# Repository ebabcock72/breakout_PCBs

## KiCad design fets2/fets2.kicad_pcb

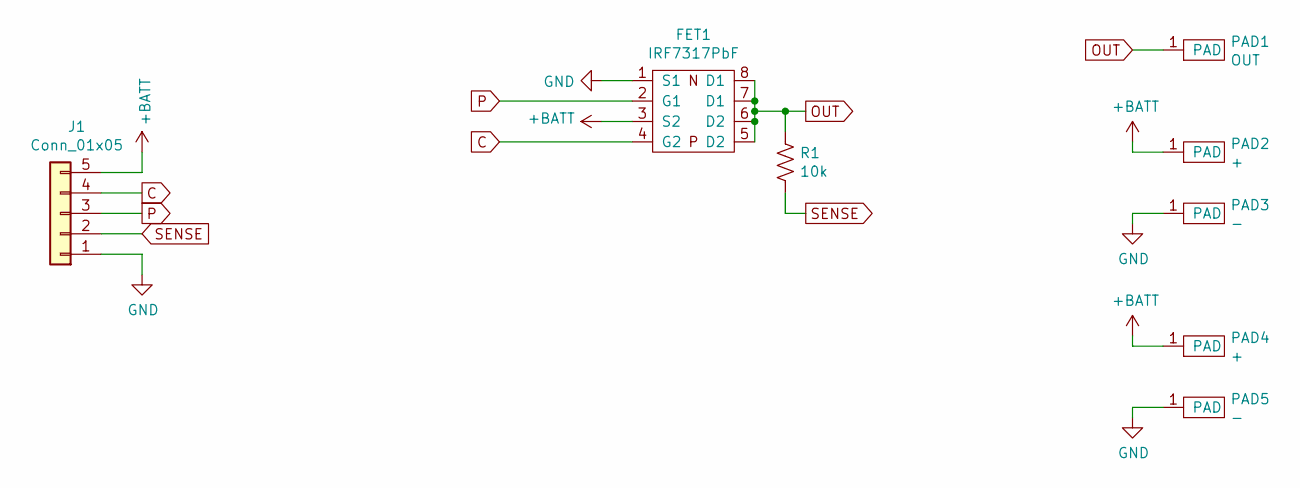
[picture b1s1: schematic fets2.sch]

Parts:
FET1: IRF7317PbF
J1: Conn_01x05; PinHeader_1x05_P2.54mm_Vertical
PAD1: OUT; TestPoint_Pad_2.0x2.0mm
PAD2, PAD4: +; TestPoint_Pad_2.0x2.0mm
PAD3, PAD5: -; TestPoint_Pad_2.0x2.0mm
R1: 10k; R_0603_1608Metric

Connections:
+BATT: FET1.3 (S2), J1.5, PAD2.1, PAD4.1
C: FET1.4 (G2), J1.4
GND: FET1.1 (S1), J1.1, PAD3.1, PAD5.1
OUT: FET1.5 (D2), FET1.6 (D2), FET1.7 (D1), FET1.8 (D1), PAD1.1, R1.2
P: FET1.2 (G1), J1.3
SENSE: J1.2, R1.1

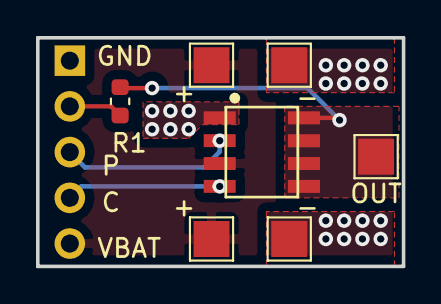
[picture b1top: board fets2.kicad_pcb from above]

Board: 2 copper layers, 20.3 x 12.7 mm, 8 parts (1 on the bottom side), 6 nets.

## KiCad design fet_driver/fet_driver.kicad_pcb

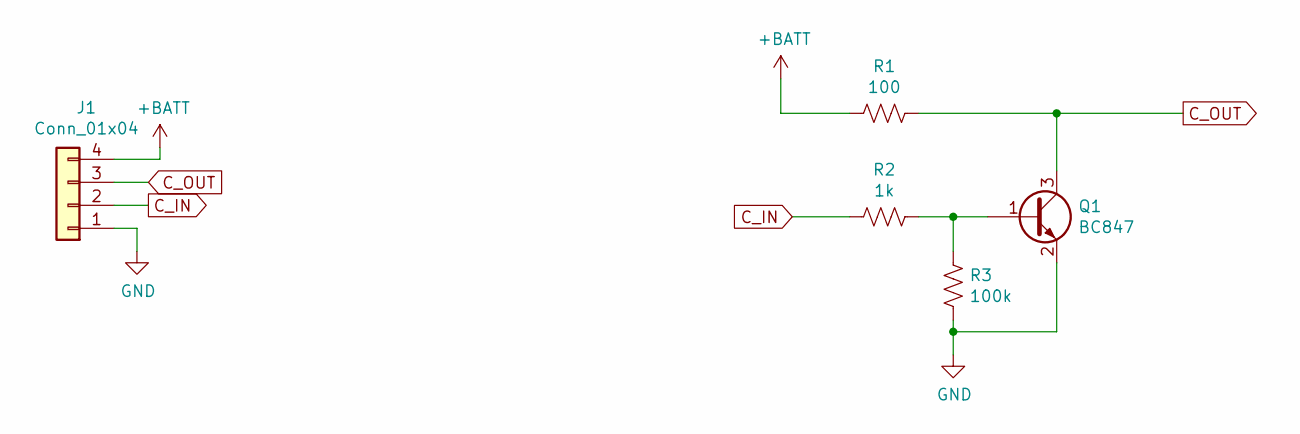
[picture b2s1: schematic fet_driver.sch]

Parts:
J1: Conn_01x04; PinHeader_1x04_P2.54mm_Vertical
Q1: BC847; SOT-23
R1: 100; R_0603_1608Metric
R2: 1k; R_0603_1608Metric
R3: 100k; R_0603_1608Metric

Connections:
+BATT: J1.4, R1.2
C_IN: J1.2, R2.2
C_OUT: J1.3, Q1.3 (C), R1.1
GND: J1.1, Q1.2 (E), R3.2
unnamed: Q1.1 (B), R2.1, R3.1

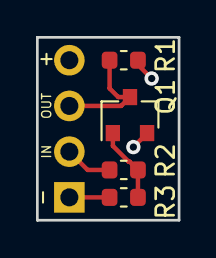
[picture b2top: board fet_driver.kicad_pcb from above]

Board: 2 copper layers, 7.9 x 10.2 mm, 5 parts (1 on the bottom side), 5 nets.

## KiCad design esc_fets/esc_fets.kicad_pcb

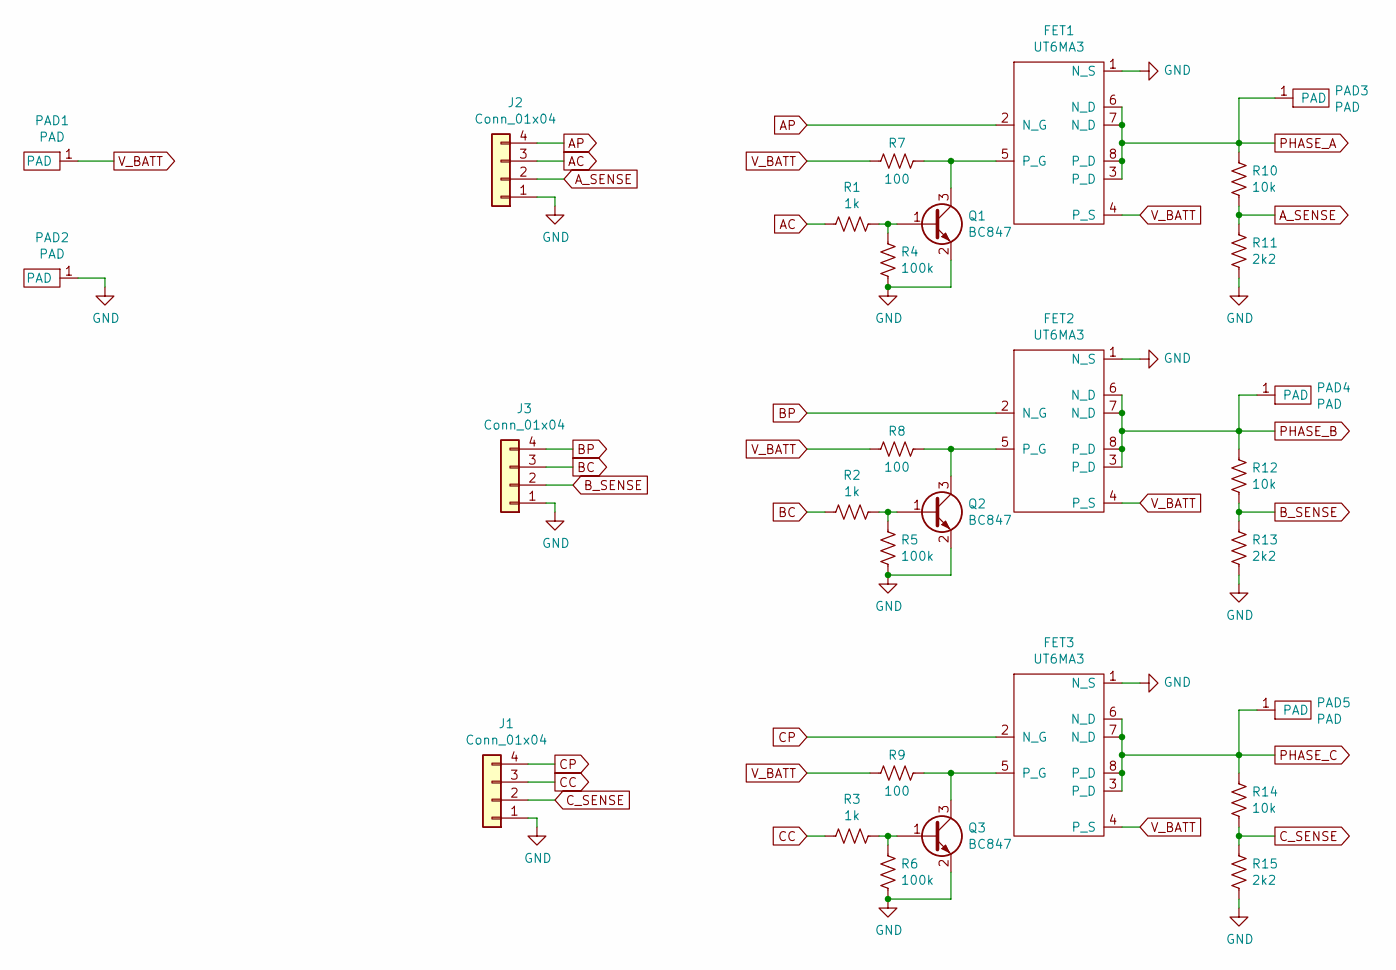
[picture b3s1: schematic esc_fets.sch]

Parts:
FET1, FET2, FET3: UT6MA3
J1, J2, J3: Conn_01x04; PinHeader_1x04_P2.54mm_Vertical
PAD1, PAD2, PAD3, PAD4, PAD5: PAD; TestPoint_Pad_3.0x3.0mm
Q1, Q2, Q3: BC847; SOT-23
R1, R2, R3: 1k; R_0603_1608Metric
R4, R5, R6: 100k; R_0603_1608Metric
R7, R8, R9: 100; R_0603_1608Metric
R10, R12, R14: 10k; R_0603_1608Metric
R11, R13, R15: 2k2; R_0603_1608Metric

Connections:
AC: J2.3, R1.2
AP: FET1.2 (N_G), J2.4
A_SENSE: J2.2, R10.1, R11.2
BC: J3.3, R2.2
BP: FET2.2 (N_G), J3.4
B_SENSE: J3.2, R12.1, R13.2
CC: J1.3, R3.2
CP: FET3.2 (N_G), J1.4
C_SENSE: J1.2, R14.1, R15.2
GND: FET1.1 (N_S), FET2.1 (N_S), FET3.1 (N_S), J1.1, J2.1, J3.1, PAD2.1, Q1.2 (E), Q2.2 (E), Q3.2 (E), R4.1, R5.1, R6.1, R11.1, R13.1, R15.1
unnamed: FET1.5 (P_G), Q1.3 (C), R7.1
unnamed: FET2.5 (P_G), Q2.3 (C), R8.1
unnamed: FET3.5 (P_G), Q3.3 (C), R9.1
unnamed: Q1.1 (B), R1.1, R4.2
unnamed: Q2.1 (B), R2.1, R5.2
unnamed: Q3.1 (B), R3.1, R6.2
PHASE_A: FET1.3 (P_D), FET1.6 (N_D), FET1.7 (N_D), FET1.8 (P_D), PAD3.1, R10.2
PHASE_B: FET2.3 (P_D), FET2.6 (N_D), FET2.7 (N_D), FET2.8 (P_D), PAD4.1, R12.2
PHASE_C: FET3.3 (P_D), FET3.6 (N_D), FET3.7 (N_D), FET3.8 (P_D), PAD5.1, R14.2
V_BATT: FET1.4 (P_S), FET2.4 (P_S), FET3.4 (P_S), PAD1.1, R7.2, R8.2, R9.2

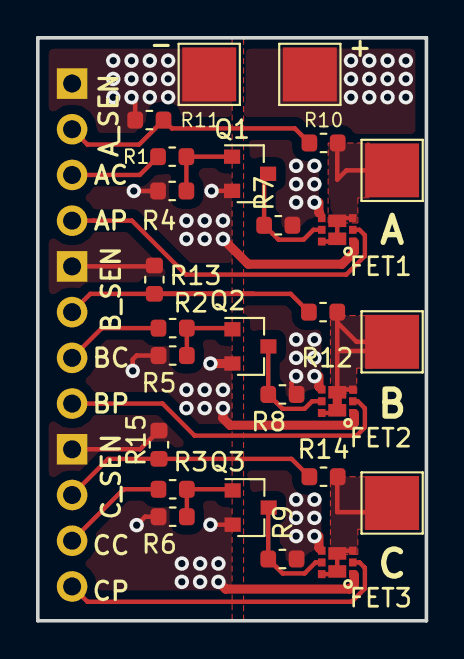
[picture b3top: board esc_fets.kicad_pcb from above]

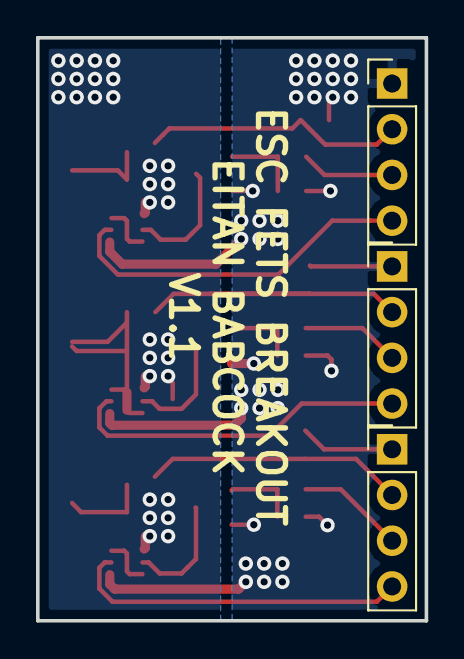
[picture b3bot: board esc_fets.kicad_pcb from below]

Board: 2 copper layers, 21.6 x 32.4 mm, 29 parts (3 on the bottom side), 20 nets.

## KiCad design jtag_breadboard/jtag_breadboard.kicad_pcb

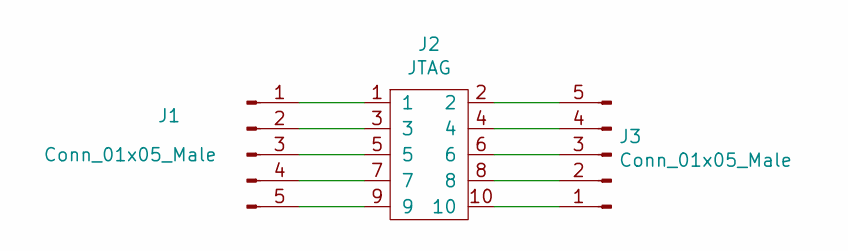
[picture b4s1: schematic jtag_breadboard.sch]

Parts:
J1, J3: Conn_01x05_Male; PinHeader_1x05_P2.54mm_Vertical
J2: JTAG

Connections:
unnamed: J1.1, J2.1
unnamed: J1.2, J2.3
unnamed: J1.3, J2.5
unnamed: J1.4, J2.7
unnamed: J1.5, J2.9
unnamed: J2.2, J3.5
unnamed: J2.4, J3.4
unnamed: J2.6, J3.3
unnamed: J2.8, J3.2
unnamed: J2.10, J3.1

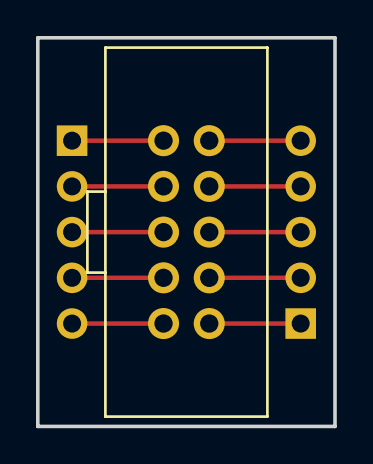
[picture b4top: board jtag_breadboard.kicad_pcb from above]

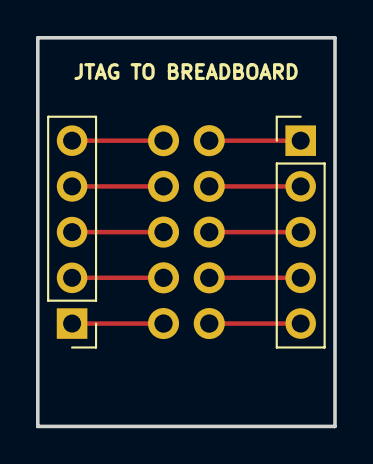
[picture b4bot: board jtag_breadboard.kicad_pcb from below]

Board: 2 copper layers, 16.5 x 21.6 mm, 3 parts (2 on the bottom side), 10 nets.

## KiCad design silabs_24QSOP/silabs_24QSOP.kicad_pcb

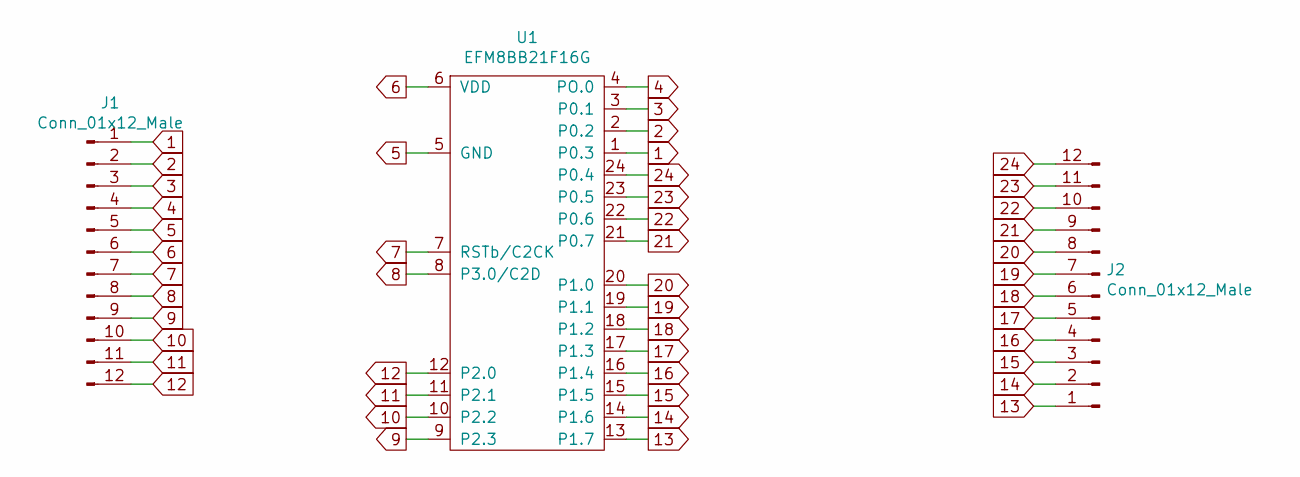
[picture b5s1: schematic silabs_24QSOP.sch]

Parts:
J1, J2: Conn_01x12_Male; PinHeader_1x12_P2.54mm_Vertical
U1: EFM8BB21F16G; efm8b21-qsop24

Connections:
1: J1.1, U1.1 (P0.3)
2: J1.2, U1.2 (P0.2)
3: J1.3, U1.3 (P0.1)
4: J1.4, U1.4 (PO.0)
5: J1.5, U1.5 (GND)
6: J1.6, U1.6 (VDD)
7: J1.7, U1.7 (RSTb/C2CK)
8: J1.8, U1.8 (P3.0/C2D)
9: J1.9, U1.9 (P2.3)
10: J1.10, U1.10 (P2.2)
11: J1.11, U1.11 (P2.1)
12: J1.12, U1.12 (P2.0)
13: J2.1, U1.13 (P1.7)
14: J2.2, U1.14 (P1.6)
15: J2.3, U1.15 (P1.5)
16: J2.4, U1.16 (P1.4)
17: J2.5, U1.17 (P1.3)
18: J2.6, U1.18 (P1.2)
19: J2.7, U1.19 (P1.1)
20: J2.8, U1.20 (P1.0)
21: J2.9, U1.21 (P0.7)
22: J2.10, U1.22 (P0.6)
23: J2.11, U1.23 (P0.5)
24: J2.12, U1.24 (P0.4)

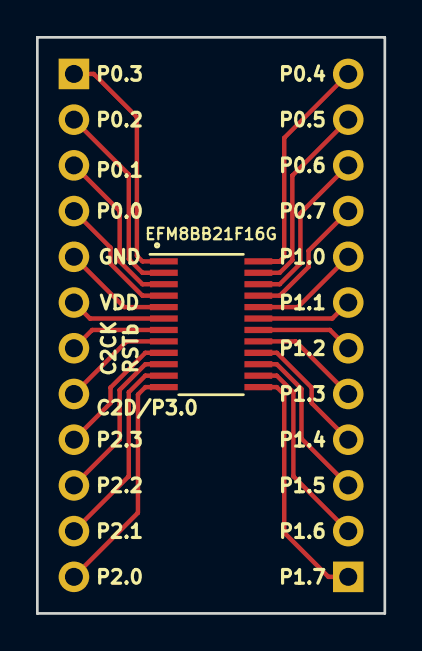
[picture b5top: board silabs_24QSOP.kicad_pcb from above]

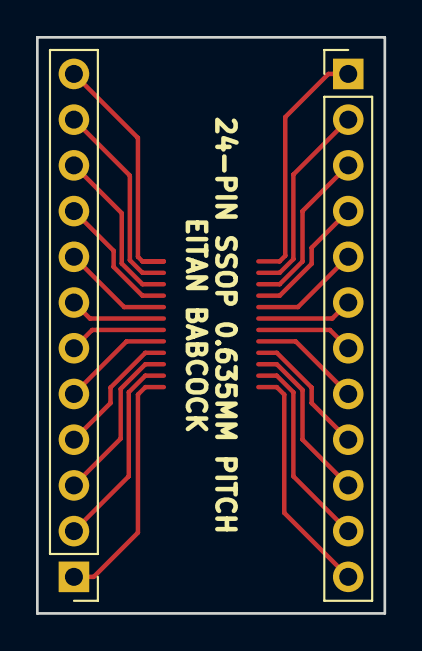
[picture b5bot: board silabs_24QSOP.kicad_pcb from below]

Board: 2 copper layers, 19.3 x 32.0 mm, 3 parts (2 on the bottom side), 24 nets.
